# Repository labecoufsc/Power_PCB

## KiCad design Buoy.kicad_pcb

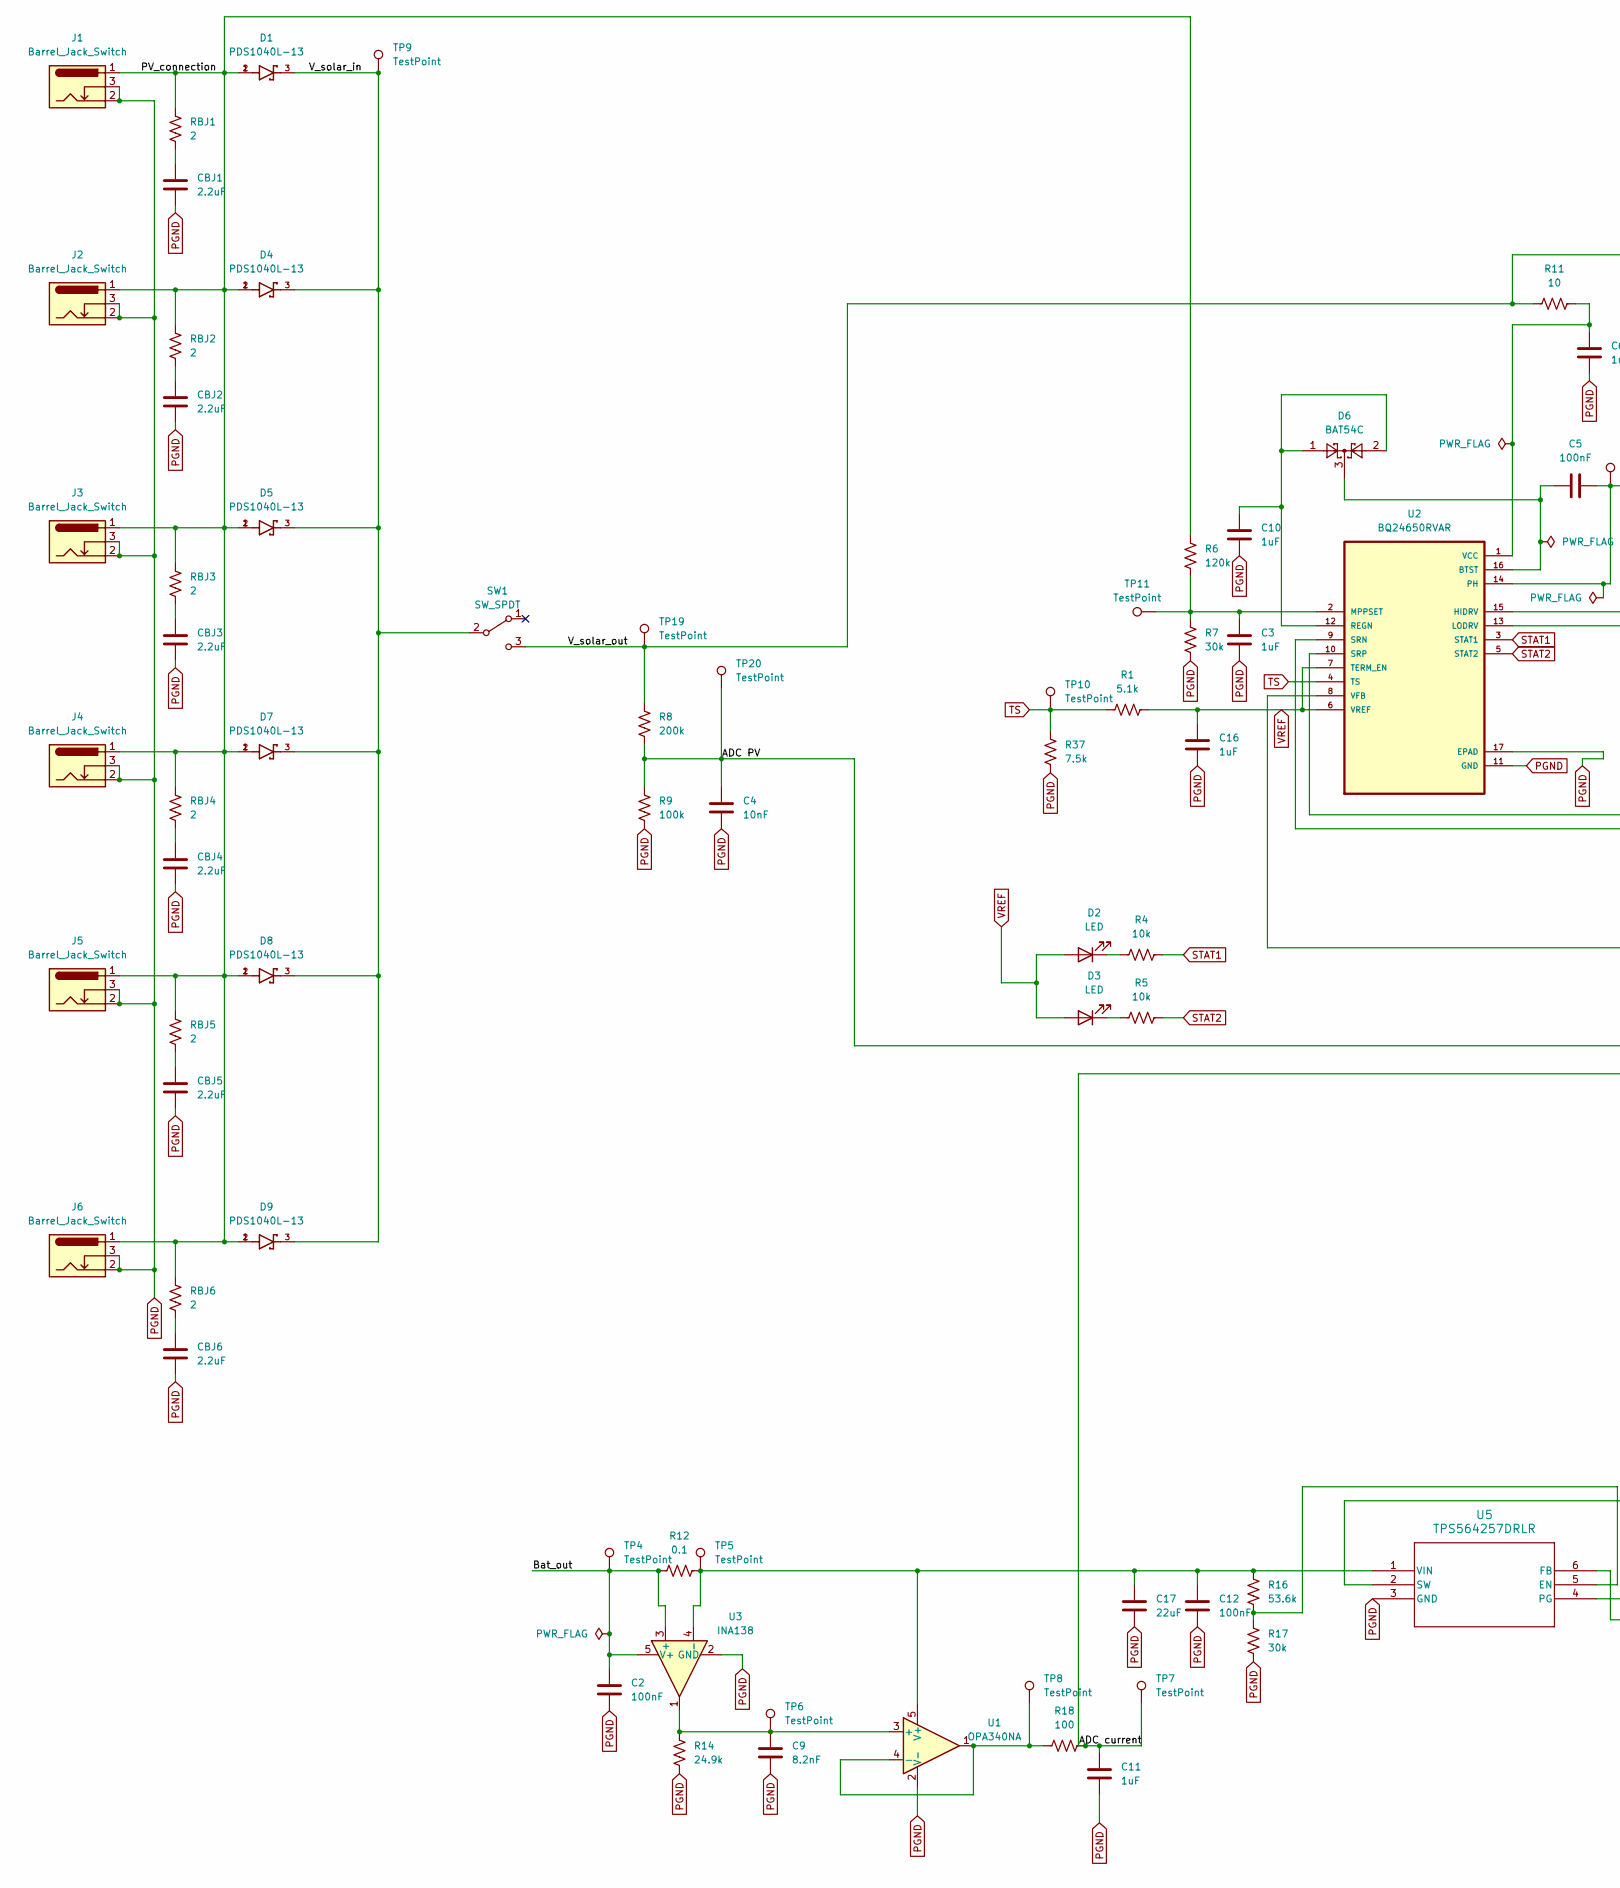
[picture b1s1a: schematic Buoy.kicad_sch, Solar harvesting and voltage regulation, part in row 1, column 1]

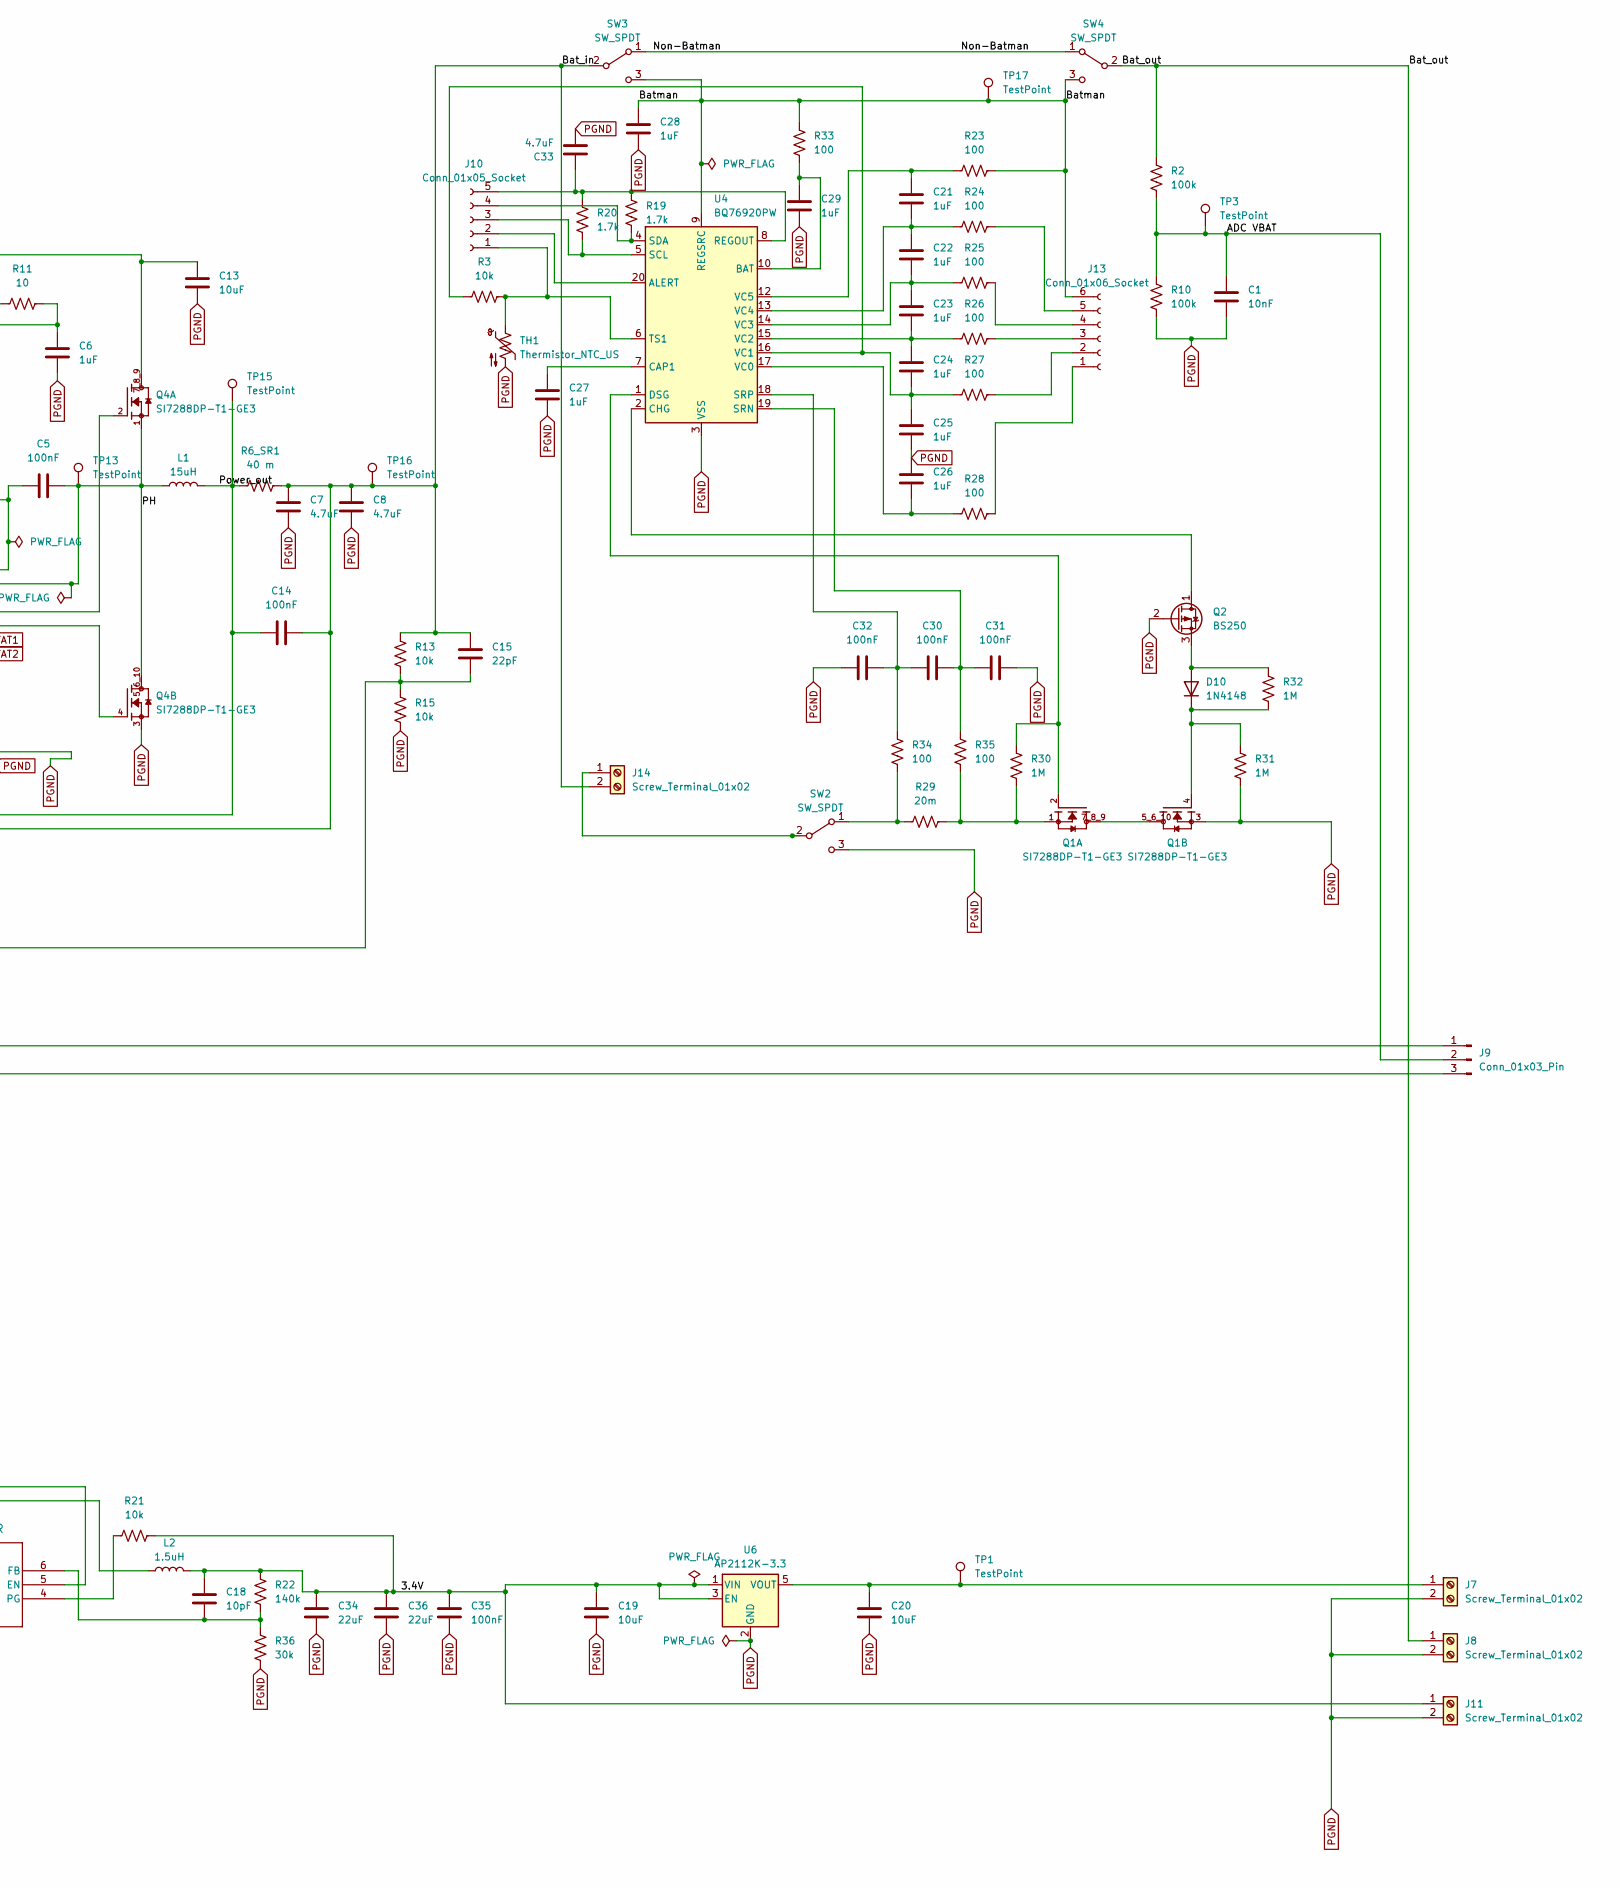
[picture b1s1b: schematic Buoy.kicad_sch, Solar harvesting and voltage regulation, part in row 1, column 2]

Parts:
C1, C4: 10nF; C_0805_2012Metric_Pad1.18x1.45mm_HandSolder
C2, C5, C14, C30, C31, C32, C35: 100nF; C_0805_2012Metric_Pad1.18x1.45mm_HandSolder
C3, C6, C10, C16, C21, C22, C23, C24, C25, C26: 1uF; C_0805_2012Metric_Pad1.18x1.45mm_HandSolder
C7, C8: 4.7uF; C_1210_3225Metric_Pad1.33x2.70mm_HandSolder
C9: 8.2nF; C_0603_1608Metric_Pad1.08x0.95mm_HandSolder
C11, C27, C28, C29: 1uF; C_1210_3225Metric_Pad1.33x2.70mm_HandSolder
C12: 100nF; C_0603_1608Metric_Pad1.08x0.95mm_HandSolder
C13, C19, C20: 10uF; C_1206_3216Metric_Pad1.33x1.80mm_HandSolder
C15: 22pF; C_0603_1608Metric_Pad1.08x0.95mm_HandSolder
C17: 22uF; C_1210_3225Metric_Pad1.33x2.70mm_HandSolder
C18: 10pF; C_0402_1005Metric_Pad0.74x0.62mm_HandSolder
C33: 4.7uF; C_0805_2012Metric_Pad1.18x1.45mm_HandSolder
C34, C36: 22uF; C_0805_2012Metric_Pad1.18x1.45mm_HandSolder
CBJ1, CBJ2, CBJ3, CBJ4, CBJ5, CBJ6: 2.2uF; C_1210_3225Metric_Pad1.33x2.70mm_HandSolder
D1, D4, D5, D7, D8, D9: PDS1040L-13; DIO_PDS1040L-13; PARTREV 13
D2, D3: LED; LEDC1608X35N
D6: BAT54C; SOT-23_Handsoldering
D10: 1N4148; D_SOD-323_HandSoldering
J1, J2, J3, J4, J5, J6: Barrel_Jack_Switch; XKB_DC-005-5A-2.0
J7, J8, J11, J14: Screw_Terminal_01x02; CONN_1729128_PXC
J9: Conn_01x03_Pin; PinHeader_1x03_P2.54mm_Vertical_SMD_Pin1Right
J10: Conn_01x05_Socket; PinHeader_1x05_P2.54mm_Vertical_SMD_Pin1Right
J13: Conn_01x06_Socket; PinHeader_1x06_P2.54mm_Vertical_SMD_Pin1Right
L1: 15uH; L_Koher_MDA1350_13.5x12.6mm_1
L2: 1.5uH; L_Vishay_IHLP-2020
Q1, Q4: SI7288DP-T1-GE3; TRANS_SI7288DP-T1-GE3; PARTREV A
Q2: BS250; SOT95P240X110-3N
R1: 5.1k; R_1206_3216Metric_Pad1.30x1.75mm_HandSolder
R2, R9, R10: 100k; R_0402_1005Metric_Pad0.72x0.64mm_HandSolder
R3, R4, R5, R13, R15: 10k; R_0805_2012Metric_Pad1.20x1.40mm_HandSolder
R6: 120k; R_0603_1608Metric_Pad0.98x0.95mm_HandSolder
R6_SR1: 40 m; R_2010_5025Metric_Pad1.40x2.65mm_HandSolder
R7, R17, R36: 30k; R_0603_1608Metric_Pad0.98x0.95mm_HandSolder
R8: 200k; R_0603_1608Metric_Pad0.98x0.95mm_HandSolder
R11: 10; R_1206_3216Metric_Pad1.30x1.75mm_HandSolder
R12: 0.1; R_2010_5025Metric_Pad1.40x2.65mm_HandSolder
R14: 24.9k; R_0402_1005Metric_Pad0.72x0.64mm_HandSolder
R16: 53.6k; R_0402_1005Metric_Pad0.72x0.64mm_HandSolder
R18, R23, R24, R25, R26, R27, R28, R33, R34, R35: 100; R_1210_3225Metric_Pad1.30x2.65mm_HandSolder
R19, R20: 1.7k; R_1206_3216Metric_Pad1.30x1.75mm_HandSolder
R21: 10k; R_0402_1005Metric_Pad0.72x0.64mm_HandSolder
R22: 140k; R_0805_2012Metric_Pad1.20x1.40mm_HandSolder
R29: 20m; R_2010_5025Metric_Pad1.40x2.65mm_HandSolder
R30, R31, R32: 1M; R_1206_3216Metric_Pad1.30x1.75mm_HandSolder
R37: 7.5k; R_0402_1005Metric_Pad0.72x0.64mm_HandSolder
RBJ1, RBJ2, RBJ3, RBJ4, RBJ5, RBJ6: 2; R_2512_6332Metric_Pad1.40x3.35mm_HandSolder
SW1, SW2, SW3, SW4: SW_SPDT; SW-SPDT-SW
TH1: Thermistor_NTC_US; THRMC1005X55N
TP1, TP3, TP4, TP5, TP6, TP7, TP8, TP9, TP10, TP11, TP13, TP15, TP16, TP17, TP19, TP20: TestPoint; TestPoint_Pad_1.0x1.0mm
U1: OPA340NA; SOT-23-5
U2: BQ24650RVAR; QFN50P350X350X100-17N
U3: INA138; SOT95P280X145-5N
U4: BQ76920PW; TSSOP-20_4.4x6.5mm_P0.65mm
U5: TPS564257DRLR; TPS564242DRLR_TEX
U6: AP2112K-3.3; SOT95P285X140-5N

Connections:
/3.4V: C18.1, C19.1, C34.1, C35.1, C36.1, J11.1, L2.2, R21.2, R22.1, U6.1 (VIN), U6.3 (EN); also elsewhere on the board
/ADC PV: C4.1, J9.1, R8.2, R9.1, TP20.1
/ADC VBAT: C1.1, J9.2, R2.2, R10.1, TP3.1
/ADC current: C11.1, J9.3, R18.2, TP7.1
/Bat_in: C7.1, C8.1, C14.2, C15.1, J14.2, R6_SR1.2, R13.1, SW3.2 (B), TP16.1, U2.9 (SRN)
/Bat_out: C2.1, J8.1, R2.1, R12.1, SW4.2 (B), TP4.1, U3.3 (+), U3.5 (V+)
/Batman: C28.1, J13.6, R23.2, R33.1, SW3.3 (C), SW4.3 (C), TP17.1, U4.9 (REGSRC)
/Non-Batman: SW3.1 (A), SW4.1 (A)
/PH: C5.2, L1.1, Q4.1, Q4.5_6_10, TP13.1, U2.14 (PH)
/PV_connection: D1.1, D1.2, D4.1, D4.2, D5.1, D5.2, D7.1, D7.2, D8.1, D8.2, D9.1, D9.2, J1.1, J2.1, J3.1, J4.1, J5.1, J6.1, R6.1, RBJ1.1, RBJ2.1, RBJ3.1, RBJ4.1, RBJ5.1, RBJ6.1
/Power_out: C14.1, L1.2, R6_SR1.1, TP15.1, U2.10 (SRP)
/V_solar_in: D1.3, D4.3, D5.3, D7.3, D8.3, D9.3, SW1.2 (B), TP9.1
/V_solar_out: C13.1, Q4.7_8_9, R8.1, R11.1, SW1.3 (C), TP19.1; also elsewhere on the board
unnamed: CBJ1.1, RBJ1.2
unnamed: CBJ2.1, RBJ2.2
unnamed: CBJ3.1, RBJ3.2
unnamed: CBJ4.1, RBJ4.2
unnamed: CBJ5.1, RBJ5.2
unnamed: CBJ6.1, RBJ6.2
unnamed: D2.1 (K), R4.1
unnamed: D3.1 (K), R5.1
unnamed: D10.2 (A), Q2.3 (S), R32.1
unnamed: D10.1 (K), Q1.4, R31.1, R32.2
unnamed: C20.1, J7.1, TP1.1, U6.5 (VOUT)
unnamed: J10.1, R3.2, TH1.1, U4.6 (TS1)
unnamed: J10.2, U4.20 (ALERT)
unnamed: J10.3, R20.2, U4.5 (SCL)
unnamed: J10.4, R19.2, U4.4 (SDA)
unnamed: C33.1, J10.5, R19.1, R20.1, U4.8 (REGOUT)
unnamed: J13.1, R28.2
unnamed: J13.2, R27.2
unnamed: J13.3, R26.2
unnamed: J13.4, R25.2
unnamed: J13.5, R24.2
unnamed: J14.1, SW2.2 (B)
unnamed: Q1.1, R29.2, R30.2, R35.2
unnamed: Q1.5_6_10, Q1.7_8_9
unnamed: Q2.1 (D), U4.2 (CHG)
unnamed: R29.1, R34.2, SW2.1 (A)
unnamed: C9.1, R14.1, TP6.1, U1.3 (+), U3.1
unnamed: R18.1, TP8.1, U1.1, U1.4 (-)
unnamed: C12.1, C17.1, R12.2, R16.1, TP5.1, U1.5 (V+), U3.4 (-), U5.1 (VIN)
unnamed: C5.1, D6.3, U2.16 (BTST)
unnamed: Q4.2, U2.15 (HIDRV)
unnamed: Q4.4, U2.13 (LODRV)
unnamed: C3.1, R6.2, R7.1, TP11.1, U2.2 (MPPSET)
unnamed: C10.1, D6.1, D6.2, U2.12 (REGN)
unnamed: C6.1, R11.2, U2.1 (VCC)
unnamed: C15.2, R13.2, R15.1, U2.8 (VFB)
unnamed: C29.1, R33.2, U4.10 (BAT)
unnamed: C27.1, U4.7 (CAP1)
unnamed: Q1.2, R30.1, U4.1 (DSG)
unnamed: C30.1, C31.1, R35.1, U4.19 (SRN)
unnamed: C30.2, C32.2, R34.1, U4.18 (SRP)
unnamed: C26.2, R28.1, U4.17 (VC0)
unnamed: C24.2, C25.1, R3.1, R27.1, U4.16 (VC1)
unnamed: C23.2, C24.1, R26.1, U4.15 (VC2)
unnamed: C22.2, C23.1, R25.1, U4.14 (VC3)
unnamed: C21.2, C22.1, R24.1, U4.13 (VC4)
unnamed: C21.1, R23.1, U4.12 (VC5)
unnamed: R16.2, R17.1, U5.5 (EN)
unnamed: C18.2, R22.2, R36.1, U5.6 (FB)
unnamed: R21.1, U5.4 (PG)
unnamed: L2.1, U5.2 (SW)
PGND: C1.2, C2.2, C3.2, C4.2, C6.2, C7.2, C8.2, C9.2, C10.2, C11.2, C12.2, C13.2, C16.2, C17.2, C19.2, C20.2, C25.2, C26.1, C27.2, C28.2, C29.2, C31.2, C32.1, C33.2, C34.2, C35.2, C36.2, CBJ1.2, CBJ2.2, CBJ3.2, CBJ4.2, CBJ5.2, CBJ6.2, J1.2, J1.3, J2.2, J2.3, J3.2, J3.3, J4.2, J4.3, J5.2, J5.3, J6.2, J6.3, J7.2, J8.2, J11.2, Q1.3, Q2.2 (G), Q4.3, R7.2, R9.2, R10.2, R14.2, R15.2, R17.2, R31.2, R36.2, R37.2, SW2.3 (C), TH1.2, U1.2 (V-), U2.11 (GND), U2.17 (EPAD), U3.2 (GND), U4.3 (VSS), U5.3 (GND), U6.2 (GND)
STAT1: R4.2, U2.3 (STAT1)
STAT2: R5.2, U2.5 (STAT2)
TS: R1.1, R37.1, TP10.1, U2.4 (TS)
VREF: C16.1, D2.2 (A), D3.2 (A), R1.2, U2.6 (VREF), U2.7 (TERM_EN)

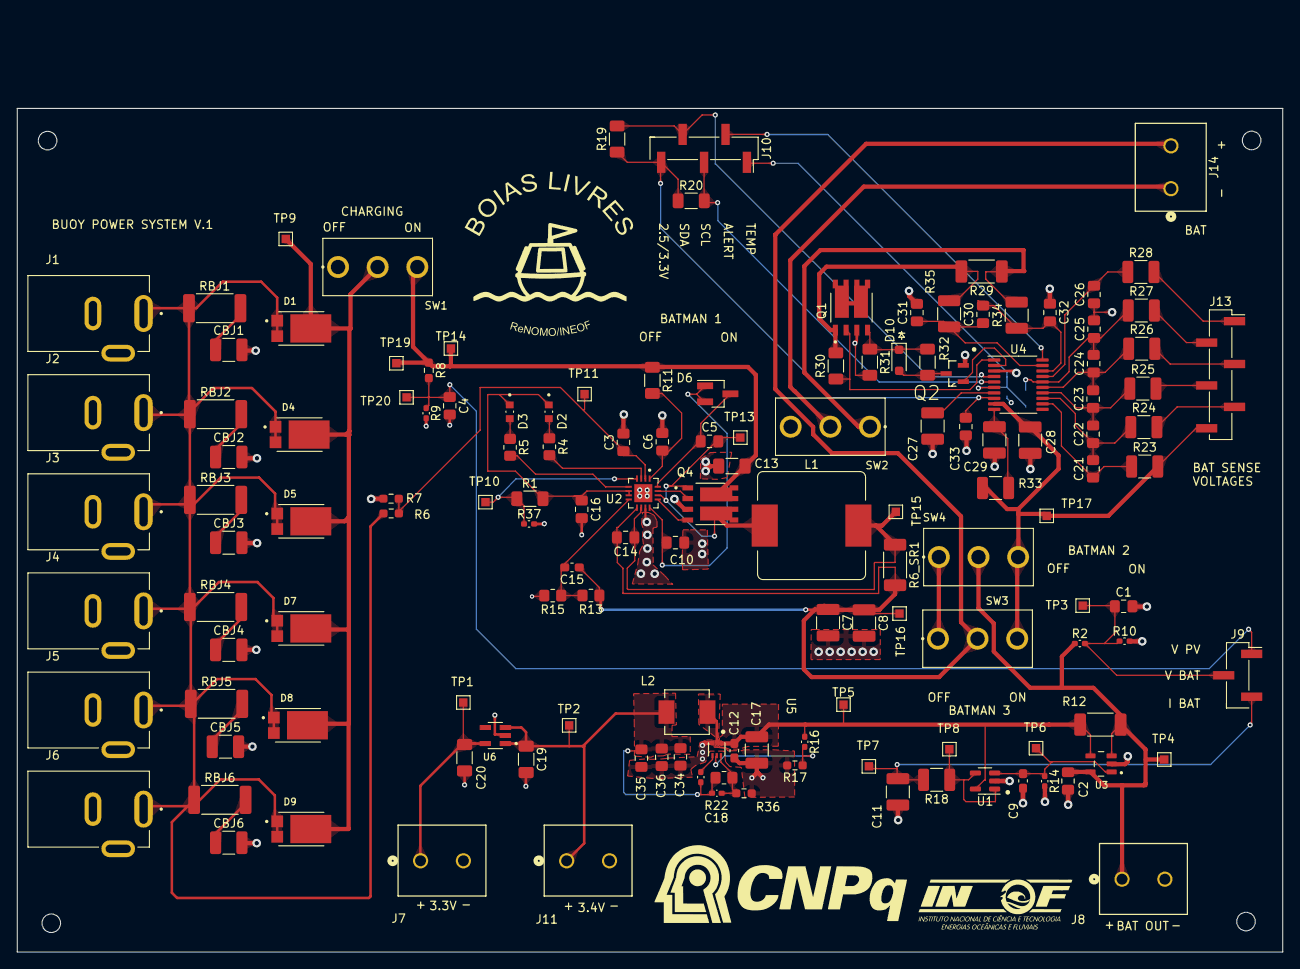
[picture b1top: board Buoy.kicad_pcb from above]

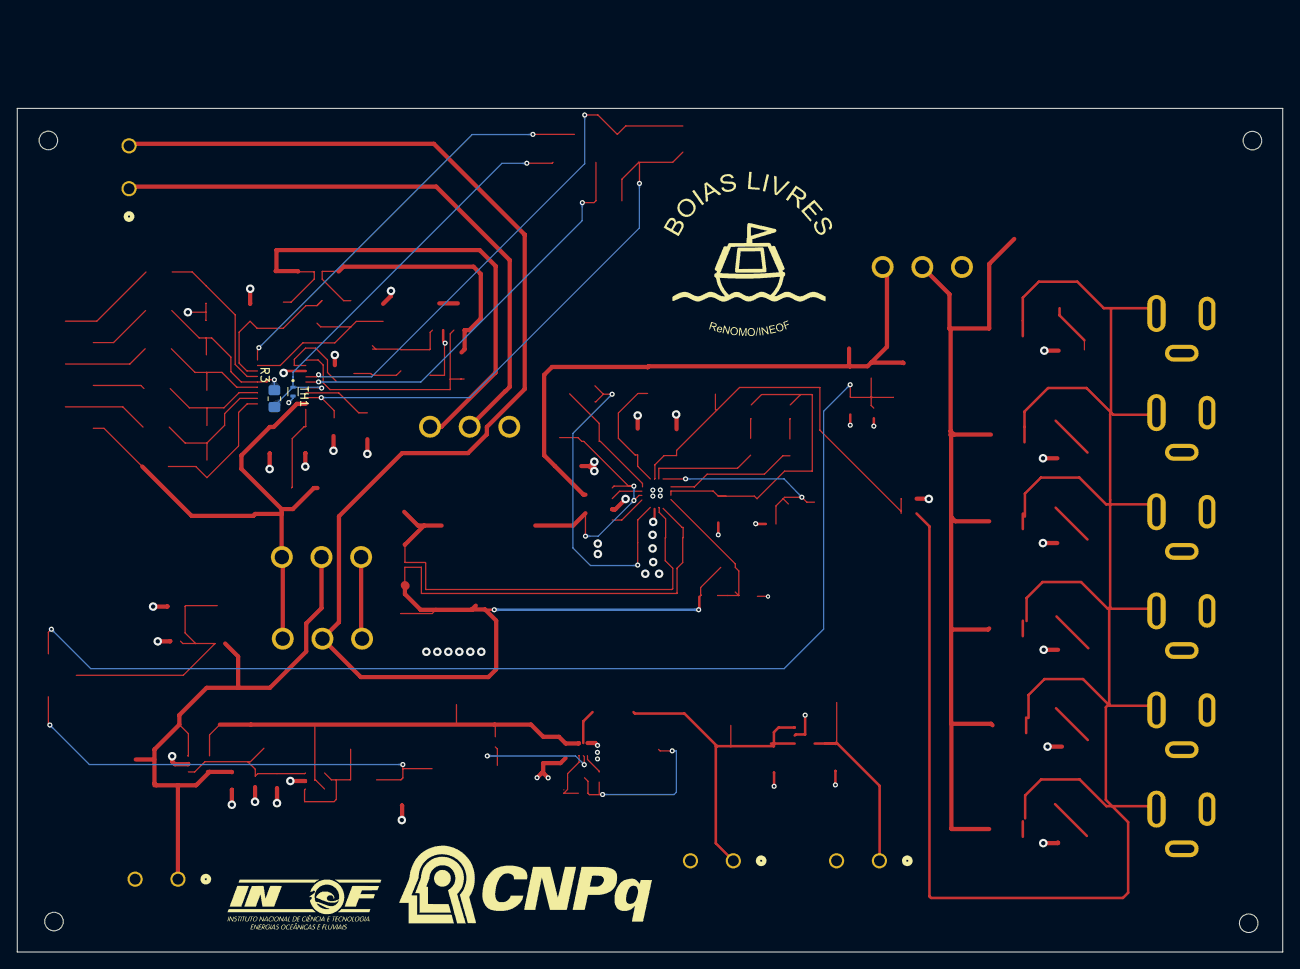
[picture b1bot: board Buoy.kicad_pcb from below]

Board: 4 copper layers, 150.0 x 110.8 mm, 145 parts (3 on the bottom side), 69 nets.

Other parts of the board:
., .#2: LOGO; CNPQ
TP2, TP14: TestPoint; TestPoint_Pad_1.0x1.0mm

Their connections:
/3.4V: TP2.1; also elsewhere on the board
/V_solar_out: TP14.1; also elsewhere on the board

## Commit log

2024-03-01 INA138 current control
2024-04-05 version 1 for consultation
2024-05-13 submitted for production
